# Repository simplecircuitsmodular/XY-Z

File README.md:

# XY-Z

This is a 16 step 2 dimensional CV sequencer. Each step is controlled by a potentiometer. The pots are laid out in a 4x4 grid, and 2 inputs (X and Y) allow you to move between rows and columns. The module is based on an ATMega 328 and is programed via the Arduino IDE.

## Files
### XY-Z_xx .brd and .sch
These are the board and schematic files needed to manufacture PCBs. Gerbers need to be generated in Eagle for manufacturing.

### XY-Z_xx.md
These are the parts lists for each module. A mouser BOM is available in this file as well.

### XY-Z.ai
These are the panels in Adobe Illustrator format. I make my panels on a laser cutter with 1/8 inch acrylic.

### XY-Z_xx.ino
This is the Arduino source code for the module. It can be uploaded using an ISP programmer.

## Updates

### 01 07OCT19
Initial upload. Design is currently untested.

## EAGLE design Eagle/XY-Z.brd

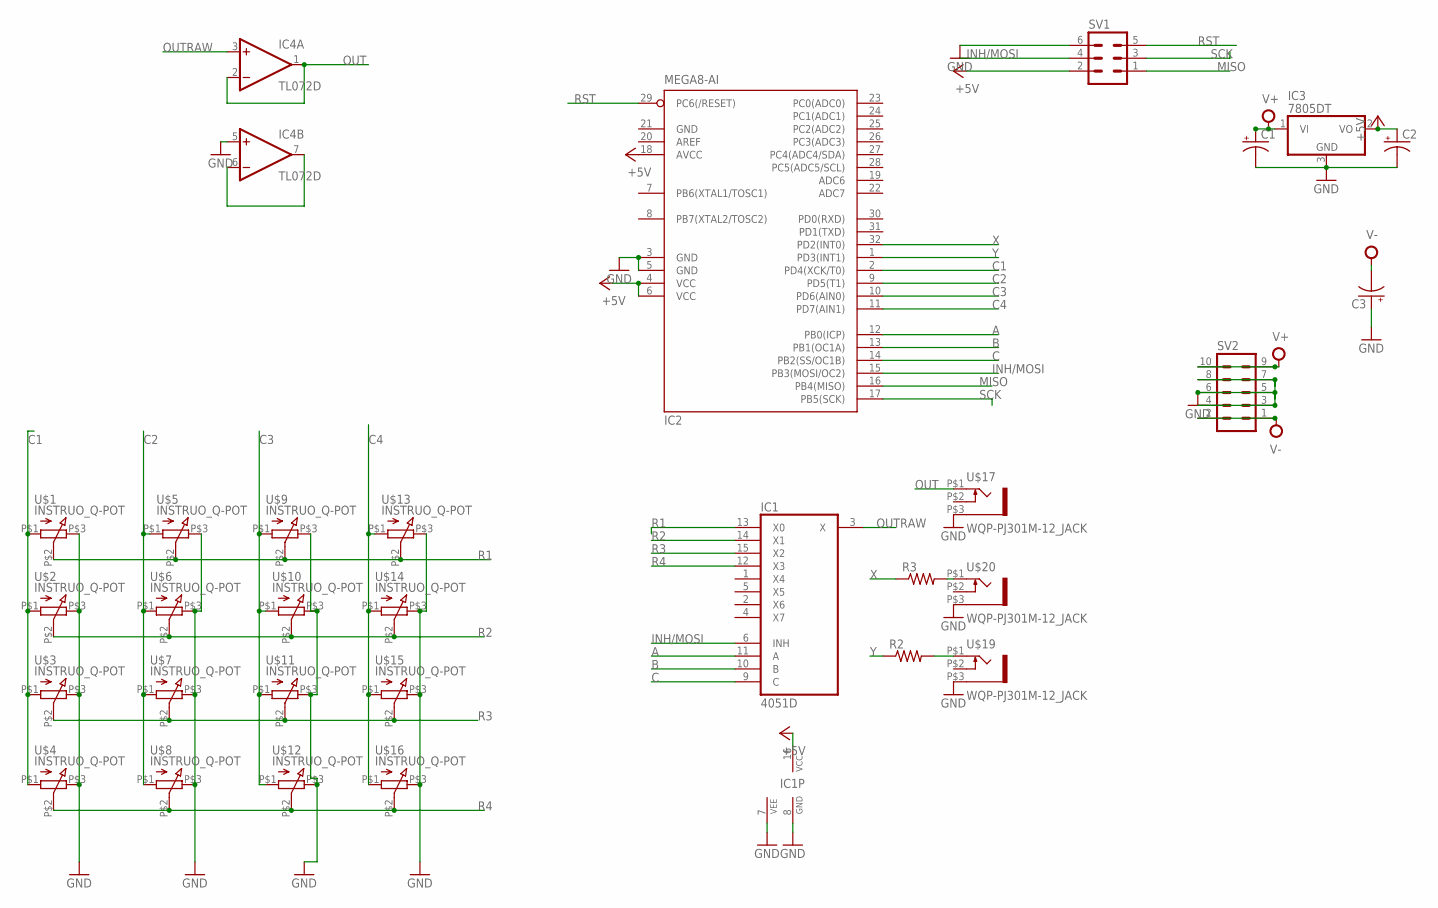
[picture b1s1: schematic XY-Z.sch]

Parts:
C1, C2, C3: CPOL-US153CLV-0505; 153CLV-0505
IC1: 4051D; SO16
IC2: MEGA8-AI; TQFP32-08
IC3: 7805DT; TO252
IC4: TL072D; SO08
R2, R3: R-US_M0805; M0805
SV1: MA03-2
SV2: MA05-2
U$1, U$2, U$3, U$4, U$5, U$6, U$7, U$8, U$9, U$10, U$11, U$12, U$13, U$14, U$15, U$16: INSTRUO_Q-POT
U$17, U$19, U$20: WQP-PJ301M-12_JACK

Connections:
+5V: C2.+, IC1.16 (VCC), IC2.4 (VCC), IC2.6 (VCC), IC2.18 (AVCC), IC3.2 (VO), SV1.2
A: IC1.11 (A), IC2.12 (PB0(ICP))
B: IC1.10 (B), IC2.13 (PB1(OC1A))
C: IC1.9 (C), IC2.14 (PB2(SS/OC1B))
C1: IC2.2 (PD4(XCK/T0)), U$1.P$1 (1), U$2.P$1 (1), U$3.P$1 (1), U$4.P$1 (1)
C2: IC2.9 (PD5(T1)), U$5.P$1 (1), U$6.P$1 (1), U$7.P$1 (1), U$8.P$1 (1)
C3: IC2.10 (PD6(AIN0)), U$9.P$1 (1), U$10.P$1 (1), U$11.P$1 (1), U$12.P$1 (1)
C4: IC2.11 (PD7(AIN1)), U$13.P$1 (1), U$14.P$1 (1), U$15.P$1 (1), U$16.P$1 (1)
GND: C1.-, C2.-, C3.+, IC1.7 (VEE), IC1.8 (GND), IC2.3 (GND), IC2.5 (GND), IC2.21 (GND), IC3.3 (GND), IC4.5 (+IN), SV1.6, SV2.3, SV2.4, SV2.5, SV2.6, SV2.7, SV2.8, U$1.P$3 (3), U$2.P$3 (3), U$3.P$3 (3), U$4.P$3 (3), U$5.P$3 (3), U$6.P$3 (3), U$7.P$3 (3), U$8.P$3 (3), U$9.P$3 (3), U$10.P$3 (3), U$11.P$3 (3), U$12.P$3 (3), U$13.P$3 (3), U$14.P$3 (3), U$15.P$3 (3), U$16.P$3 (3), U$17.P$3 (1), U$19.P$3 (1), U$20.P$3 (1)
INH/MOSI: IC1.6 (INH), IC2.15 (PB3(MOSI/OC2)), SV1.4
MISO: IC2.16 (PB4(MISO)), SV1.1
unnamed: R2.2, U$19.P$1 (2)
unnamed: R3.2, U$20.P$1 (2)
unnamed: IC4.6 (-IN), IC4.7 (OUT)
OUT: IC4.1 (OUT), IC4.2 (-IN), U$17.P$1 (2)
OUTRAW: IC1.3 (X), IC4.3 (+IN)
R1: IC1.13 (X0), U$1.P$2 (2), U$5.P$2 (2), U$9.P$2 (2), U$13.P$2 (2)
R2: IC1.14 (X1), U$2.P$2 (2), U$6.P$2 (2), U$10.P$2 (2), U$14.P$2 (2)
R3: IC1.15 (X2), U$3.P$2 (2), U$7.P$2 (2), U$11.P$2 (2), U$15.P$2 (2)
R4: IC1.12 (X3), U$4.P$2 (2), U$8.P$2 (2), U$12.P$2 (2), U$16.P$2 (2)
RST: IC2.29 (PC6(/RESET)), SV1.5
SCK: IC2.17 (PB5(SCK)), SV1.3
V+: C1.+, IC3.1 (VI), IC4.8 (V+), SV2.9, SV2.10
V-: C3.-, IC4.4 (V-), SV2.1, SV2.2
X: IC2.32 (PD2(INT0)), R3.1
Y: IC2.1 (PD3(INT1)), R2.1

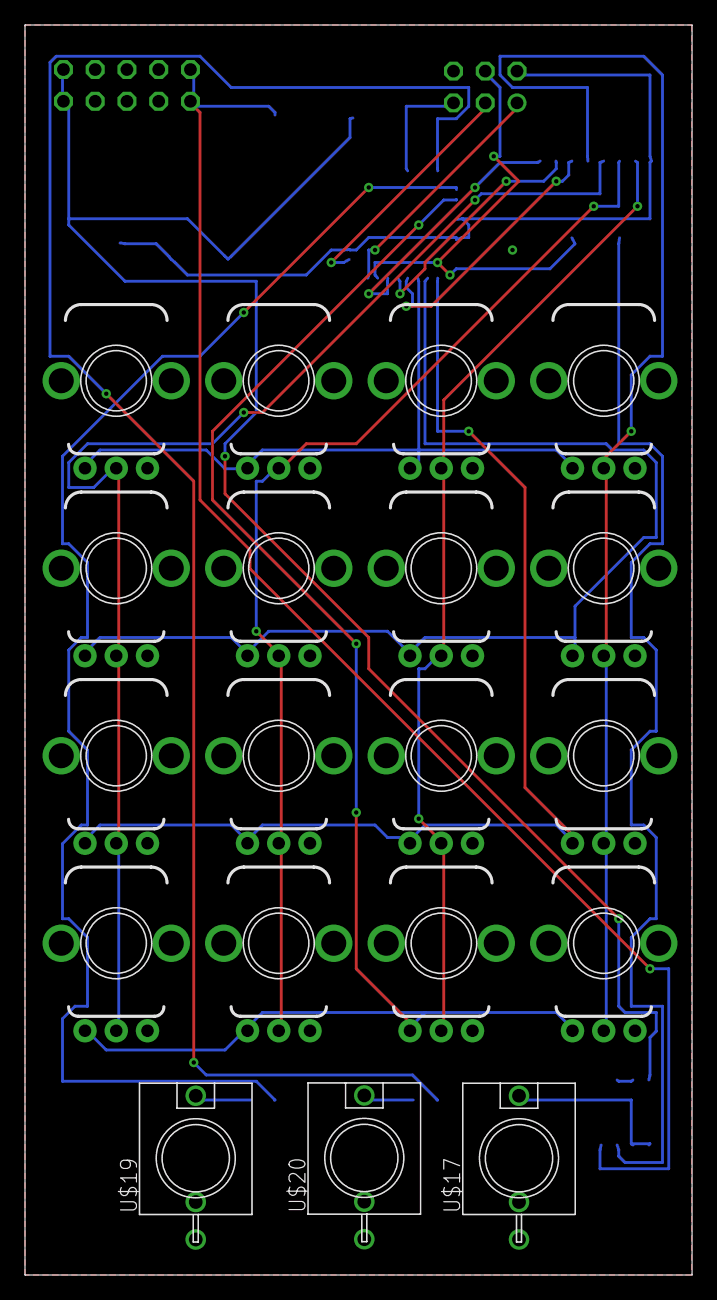
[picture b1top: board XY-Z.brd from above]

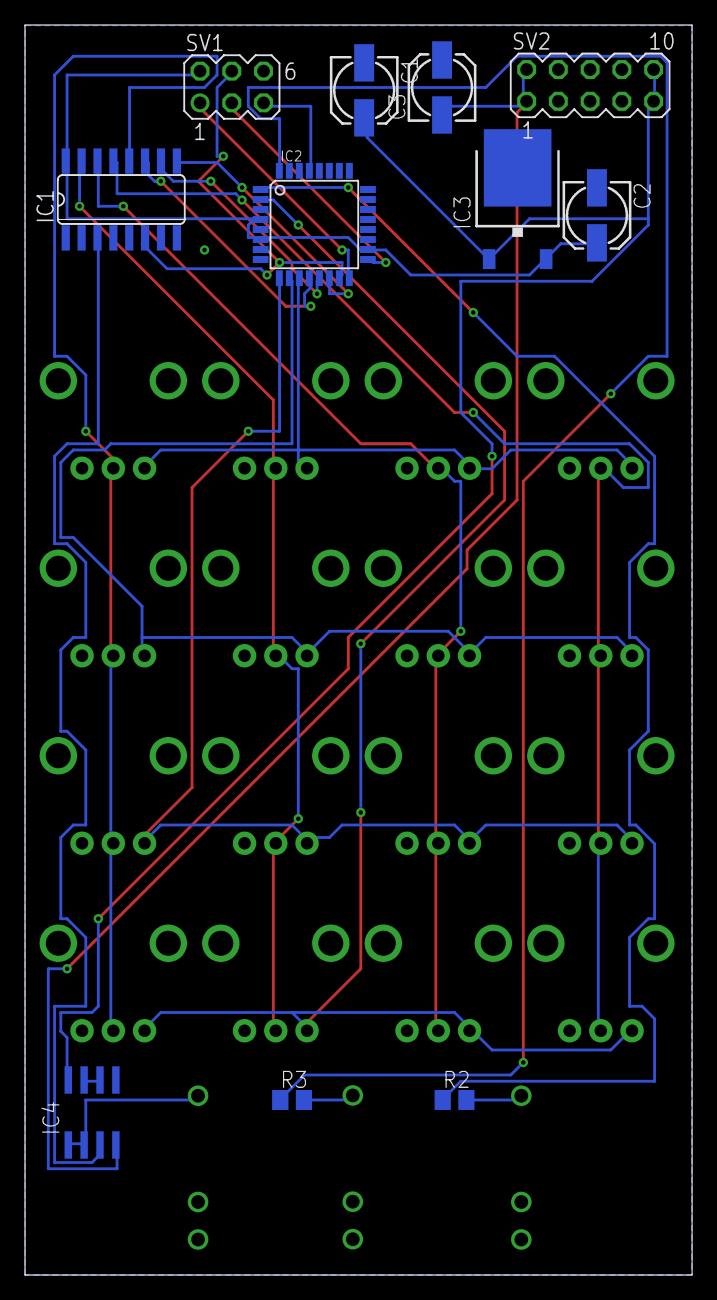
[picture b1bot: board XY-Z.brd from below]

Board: 2 copper layers, 53.4 x 100.0 mm, 30 parts (11 on the bottom side), 26 nets.

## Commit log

2019-10-07 Add panel outline
2020-02-20 Remove incorrect parts list
